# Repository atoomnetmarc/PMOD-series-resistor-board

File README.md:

# PMOD-series-resistor-board

My [Kicad library](https://github.com/atoomnetmarc/ATOOMNETKICAD) is used in this project.

# Soldering instructions

Solder RN1, RN2, RN3 and RN4.

Measure with ohmmeter between J1+J2 and J3+4 for solder bridges and correct if needed.

Solder the rest of the headers.

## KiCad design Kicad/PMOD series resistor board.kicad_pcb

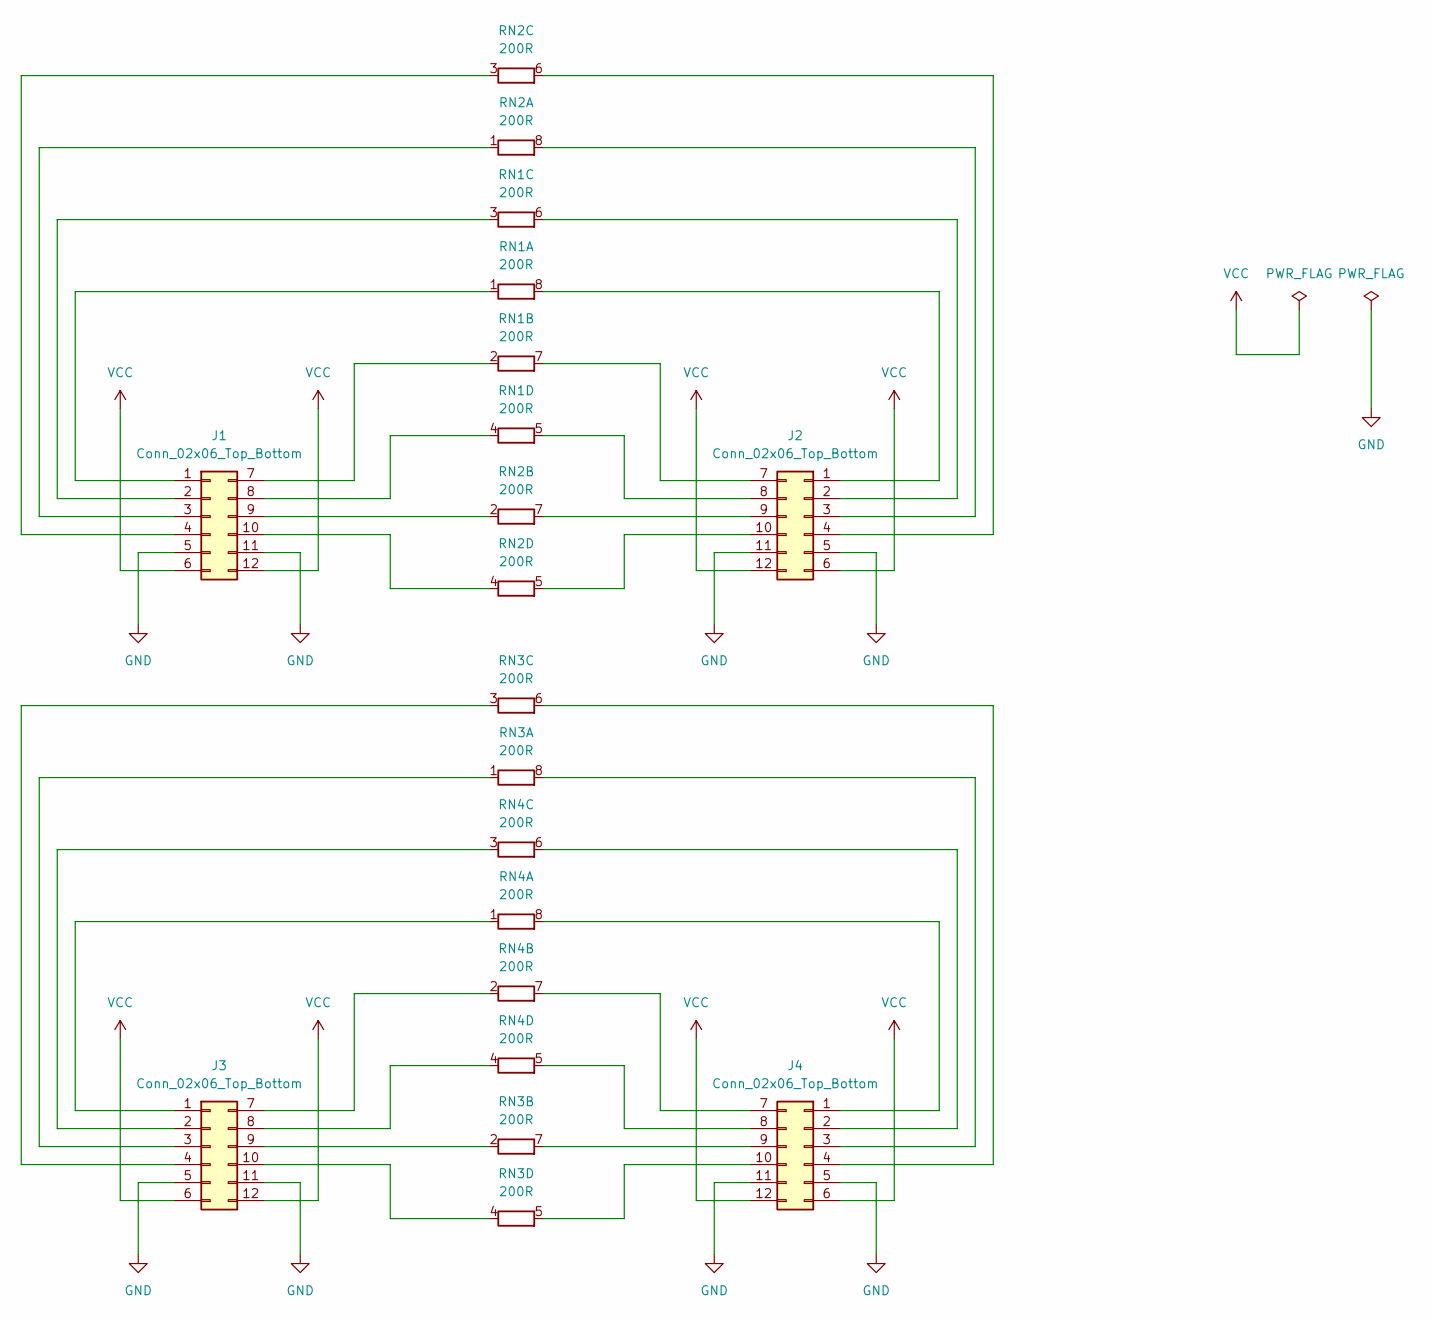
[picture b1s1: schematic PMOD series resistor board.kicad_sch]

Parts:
J1, J3: Conn_02x06_Top_Bottom; PinHeader_2x06_P2.54mm_Horizontal_Top_Bottom
J2, J4: Conn_02x06_Top_Bottom; PinSocket_2x06_P2.54mm_Horizontal_Top_Bottom
RN1, RN2, RN3, RN4: 200R; R_Array_Convex_4x0603

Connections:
GND: J1.5, J1.11, J2.5, J2.11, J3.5, J3.11, J4.5, J4.11
unnamed: J1.1, RN1.1 (R1.1)
unnamed: J2.1, RN1.8 (R1.2)
unnamed: J2.2, RN1.6 (R3.2)
unnamed: J2.3, RN2.8 (R1.2)
unnamed: J2.4, RN2.6 (R3.2)
unnamed: J2.9, RN2.7 (R2.2)
unnamed: J2.10, RN2.5 (R4.2)
unnamed: J3.1, RN4.1 (R1.1)
unnamed: J3.2, RN4.3 (R3.1)
unnamed: J3.3, RN3.1 (R1.1)
unnamed: J3.4, RN3.3 (R3.1)
unnamed: J3.7, RN4.2 (R2.1)
unnamed: J3.8, RN4.4 (R4.1)
unnamed: J3.9, RN3.2 (R2.1)
unnamed: J3.10, RN3.4 (R4.1)
unnamed: J4.1, RN4.8 (R1.2)
unnamed: J4.2, RN4.6 (R3.2)
unnamed: J4.3, RN3.8 (R1.2)
unnamed: J4.4, RN3.6 (R3.2)
unnamed: J4.7, RN4.7 (R2.2)
unnamed: J4.8, RN4.5 (R4.2)
unnamed: J1.7, RN1.2 (R2.1)
unnamed: J1.2, RN1.3 (R3.1)
unnamed: J1.8, RN1.4 (R4.1)
unnamed: J2.8, RN1.5 (R4.2)
unnamed: J2.7, RN1.7 (R2.2)
unnamed: J1.3, RN2.1 (R1.1)
unnamed: J1.9, RN2.2 (R2.1)
unnamed: J1.4, RN2.3 (R3.1)
unnamed: J1.10, RN2.4 (R4.1)
unnamed: J4.10, RN3.5 (R4.2)
unnamed: J4.9, RN3.7 (R2.2)
VCC: J1.6, J1.12, J2.6, J2.12, J3.6, J3.12, J4.6, J4.12

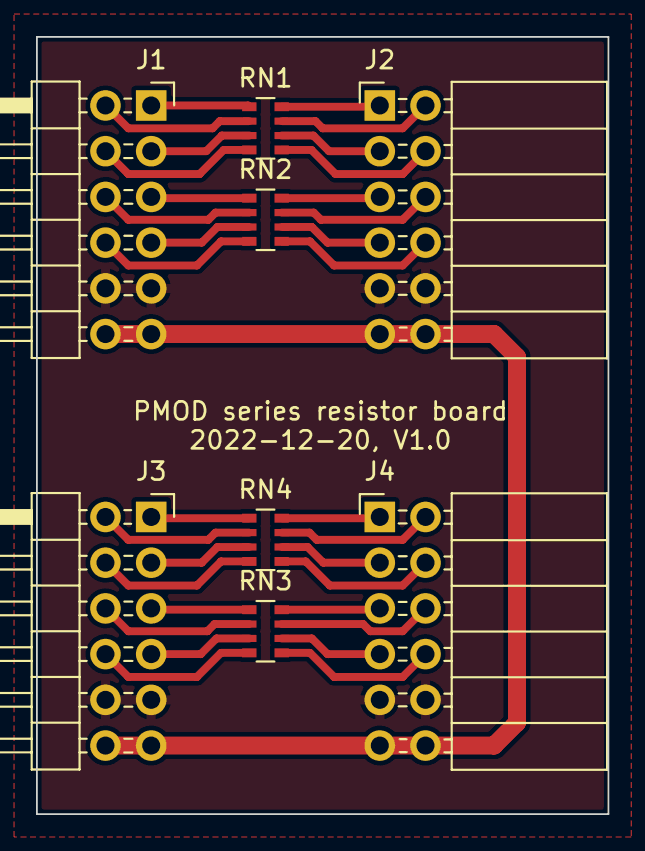
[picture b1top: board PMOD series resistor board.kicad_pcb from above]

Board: 2 copper layers, 31.8 x 43.2 mm, 8 parts (0 on the bottom side), 34 nets.

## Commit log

2022-11-21 Initial commit.
2022-12-06 Add real photo and soldering instructions.

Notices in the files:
Kicad/PMOD series resistor board.kicad_pcb:
Apache License, version 2.0
README.md:
License: Apache 2.0
